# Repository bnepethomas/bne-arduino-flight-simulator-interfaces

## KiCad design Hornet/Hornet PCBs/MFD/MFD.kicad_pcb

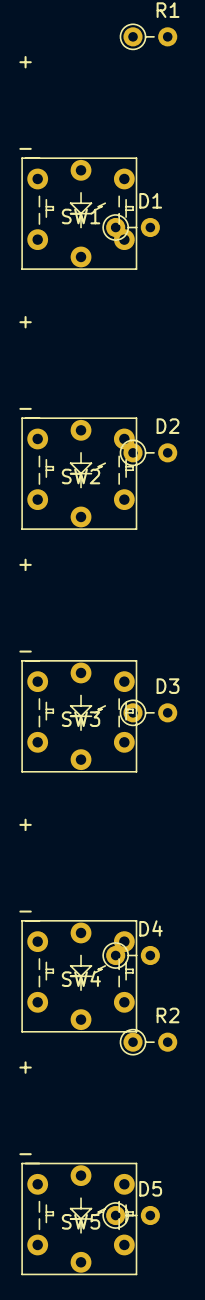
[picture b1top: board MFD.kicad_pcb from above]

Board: 2 copper layers, 12 parts (0 on the bottom side), 13 nets, no tracks yet.

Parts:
D1, D2, D3, D4, D5: D; PT_R_Axial_DIN0204_L3.6mm_D1.6mm_P2.54mm_Vertical
R1, R2: R; PT_R_Axial_DIN0204_L3.6mm_D1.6mm_P2.54mm_Vertical
SW1, SW2, SW3, SW4, SW5: PT_Tactile_Switch_Led; PT_Small_Tactile_Switch_With_LED

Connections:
+12V: R1.2, R2.2
GND: SW3.6, SW5.6
unnamed: D1.1, SW1.1, SW1.2
unnamed: D1.2, D2.2, D3.2, D4.2, D5.2
unnamed: D2.1, SW2.1, SW2.2
unnamed: D3.1, SW3.1, SW3.2
unnamed: D4.1, SW4.1, SW4.2
unnamed: D5.1, SW5.1, SW5.2
unnamed: R1.1, SW1.5
unnamed: R2.1, SW4.5
unnamed: SW1.6, SW2.5
unnamed: SW2.6, SW3.5
unnamed: SW4.6, SW5.5

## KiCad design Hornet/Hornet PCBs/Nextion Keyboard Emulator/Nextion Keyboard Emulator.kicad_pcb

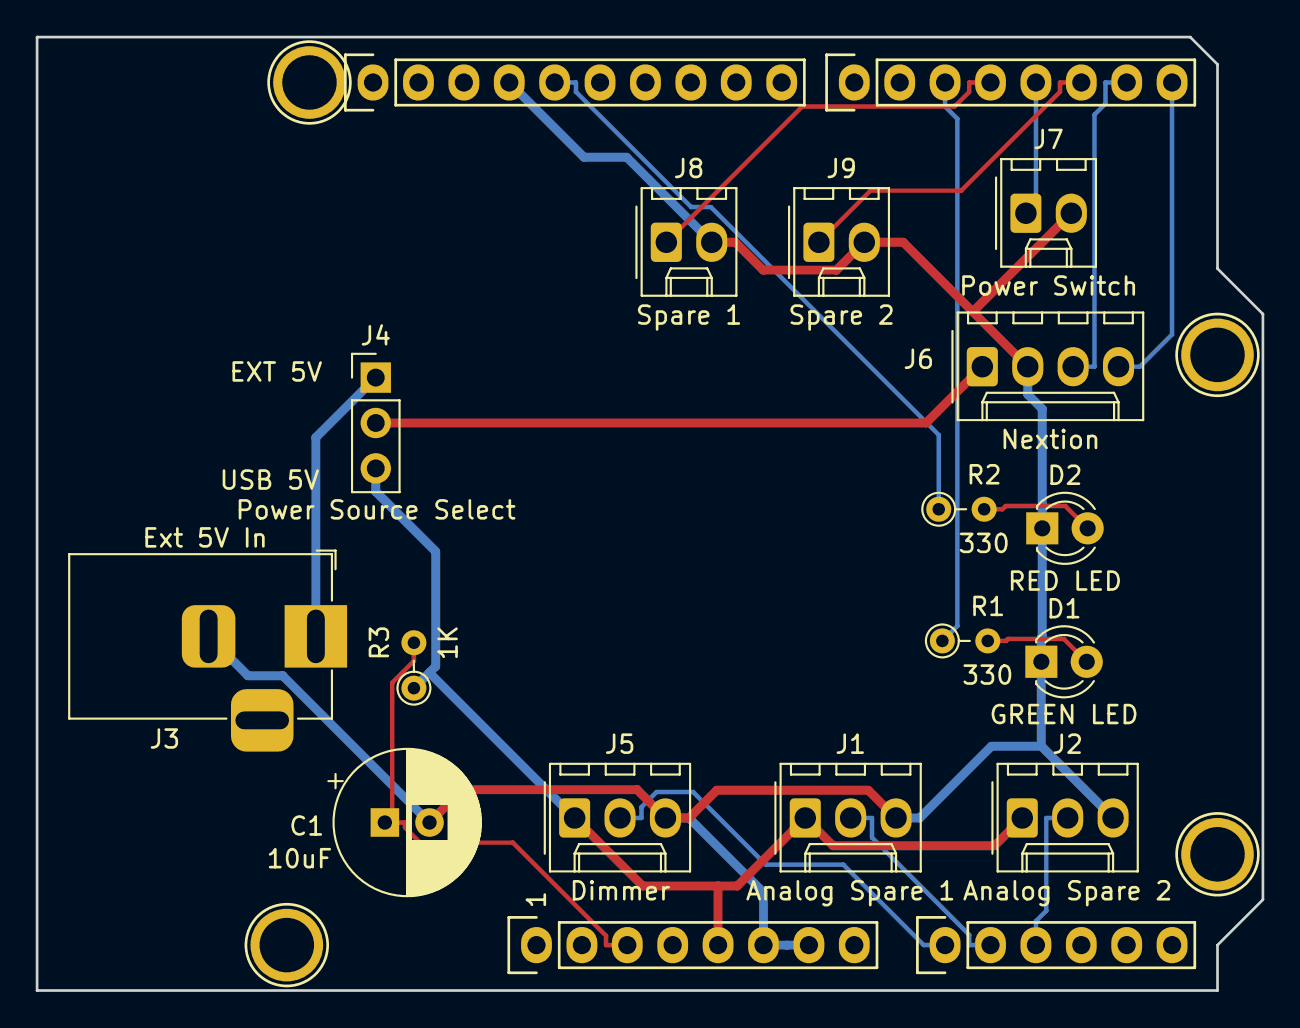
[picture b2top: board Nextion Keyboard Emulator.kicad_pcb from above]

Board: 2 copper layers, 68.6 x 53.3 mm, 23 parts (0 on the bottom side), 17 nets.

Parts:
C1: 10uF; PT_CP_Radial_D8.0mm_P2.50mm
D1: GREEN LED; LED_D3.0mm
D2: RED LED; LED_D3.0mm
J1: Analog Spare 1; Molex_1x03_P2.54mm_Vertical
J2: Analog Spare 2; Molex_1x03_P2.54mm_Vertical
J3: Ext 5V In; BarrelJack_Horizontal
J4: Power Source Select; PinHeader_1x03_P2.54mm_Vertical
J5: Dimmer; Molex_1x03_P2.54mm_Vertical
J6: Nextion; Molex_1x04_P2.54mm_Vertical
J7: Power Switch; Molex_1x02_P2.54mm_Vertical
J8: Spare 1; Molex_1x02_P2.54mm_Vertical
J9: Spare 2; Molex_1x02_P2.54mm_Vertical
P1: Power; Socket_Strip_Arduino_1x08
P2: Analog; Socket_Strip_Arduino_1x06
P3: Digital; Socket_Strip_Arduino_1x10
P4: Digital; Socket_Strip_Arduino_1x08
P5, P6, P7, P8: CONN_01X01; Arduino_1pin
R1, R2: 330; PT_R_Axial_DIN0204_L3.6mm_D1.6mm_P2.54mm_Vertical
R3: 1K; PT_R_Axial_DIN0204_L3.6mm_D1.6mm_P2.54mm_Vertical

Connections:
+5V: J1.1, J2.1, J4.3, J5.1, P1.5, R3.1
+5VD: J4.2, J6.1
/0(Rx): J6.4, P4.8
/1(Tx): J6.3, P4.7
/2: J9.1, P4.6
/3(**): J7.1, P4.5
/4: J8.1, P4.4
/5(**): P4.3, R1.1
/13(SCK): P3.5, R2.1
/A0: J5.2, P2.1
/A1: J1.2, P2.2
/A2: J2.2, P2.3
/EXT5VIN: J3.1, J4.1
/Reset: C1.1, P1.3, R3.2
GND: C1.2, D1.1, D2.1, J1.3, J2.3, J3.2, J5.3, J6.2, J7.2, J8.2, J9.2, P1.6, P1.7, P3.4
unnamed: D1.2, R1.2
unnamed: D2.2, R2.2

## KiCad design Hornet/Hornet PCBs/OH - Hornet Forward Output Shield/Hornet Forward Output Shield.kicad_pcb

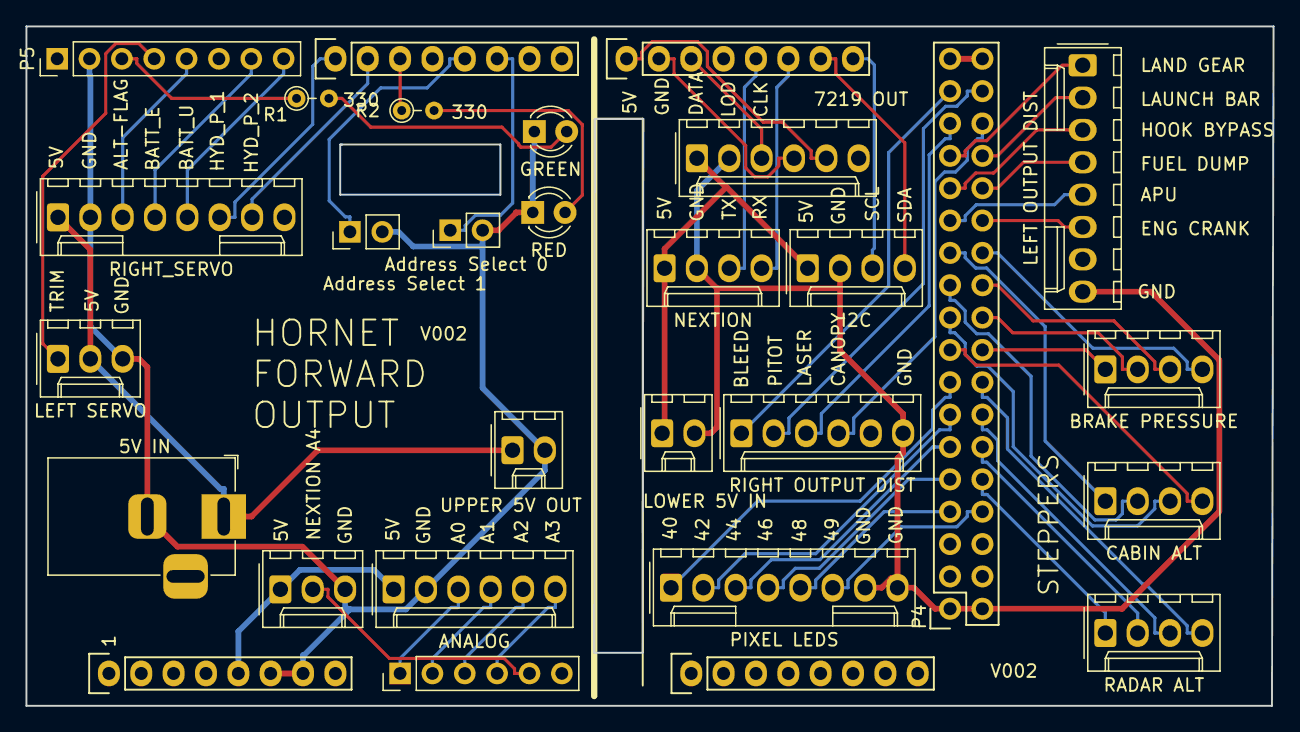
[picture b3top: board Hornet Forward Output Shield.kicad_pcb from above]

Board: 2 copper layers, 97.9 x 53.3 mm, 29 parts (0 on the bottom side), 58 nets.

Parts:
D1: GREEN; LED_D3.0mm
D2: RED; LED_D3.0mm
J1: LEFT OUTPUT DIST; Molex_1x08_P2.54mm_Vertical
J2: RIGHT OUTPUT DIST; Molex_1x06_P2.54mm_Vertical
J3: LEFT SERVO; Molex_1x03_P2.54mm_Vertical
J4: RIGHT_SERVO; Molex_1x08_P2.54mm_Vertical
J5: LOWER 5V IN; Molex_1x02_P2.54mm_Vertical
J6: UPPER 5V OUT; Molex_1x02_P2.54mm_Vertical
J7: NEXTION; Molex_1x04_P2.54mm_Vertical
J8: 7219 OUT; Molex_1x06_P2.54mm_Vertical
J9: PIXEL LEDS; Molex_1x08_P2.54mm_Vertical
J10: I2C; Molex_1x04_P2.54mm_Vertical
J11: 5V IN; BarrelJack_Horizontal
J12: CABIN ALT; Molex_1x04_P2.54mm_Vertical
J13: BRAKE PRESSURE; Molex_1x04_P2.54mm_Vertical
J14: RADAR ALT; Molex_1x04_P2.54mm_Vertical
J15: ANALOG; Molex_1x06_P2.54mm_Vertical
J16: Address Select 0; PinHeader_1x02_P2.54mm_Vertical
J17: Address Select 1; PinHeader_1x02_P2.54mm_Vertical
J18: NEXTION ANA; Molex_1x03_P2.54mm_Vertical
P1: Power; Socket_Strip_Arduino_1x08
P2: Analog; PinHeader_1x06_P2.54mm_Vertical
P3: Analog; Socket_Strip_Arduino_1x08
P4: Digital; Socket_Strip_Arduino_2x18
P5: PWM; PinHeader_1x08_P2.54mm_Vertical
P6: PWM; Socket_Strip_Arduino_1x08
P7: Communication; Socket_Strip_Arduino_1x08
R1, R2: 330; PT_R_Axial_DIN0204_L3.6mm_D1.6mm_P2.54mm_Vertical

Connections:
+5V: P4.35, P4.36
+5VL: J15.1, J18.1, P1.5
/14(Tx3): J8.5, P7.1
/15(Rx3): J8.4, P7.2
/16(Tx2): J8.3, P7.3
/18(Tx1): J7.3, P7.5
/19(Rx1): J7.4, P7.6
/20(SDA): J10.4, P7.7
/21(SCL): J10.3, P7.8
/22: J2.1, P4.33
/23: J2.2, P4.34
/24: J2.3, P4.31
/25: J2.4, P4.32
/26: J1.1, P4.29
/27: J1.2, P4.30
/28: J1.3, P4.27
/29: J1.4, P4.28
/30: J1.5, P4.25
/31: J1.6, P4.26
/32: J12.1, P4.23
/33: J13.4, P4.24
/34: J12.2, P4.21
/35: J13.3, P4.22
/36: J12.3, P4.19
/37: J13.2, P4.20
/38: J12.4, P4.17
/39: J13.1, P4.18
/40: J9.1, P4.15
/41: J14.4, P4.16
/42: J9.2, P4.13
/43: J14.3, P4.14
/44: J9.3, P4.11
/45: J14.2, P4.12
/46: J9.4, P4.9
/47: J14.1, P4.10
/48: J9.5, P4.7
/49: J9.6, P4.8
/A0: J15.3, P2.1
/A1: J15.4, P2.2
/A2: J15.5, P2.3
/A3: J15.6, P2.4
/A4: J18.2, P2.5
/ADDRESS_SELECT_0: J16.1, P6.6
/ADDRESS_SELECT_1: J17.1, P6.5
/D5: P6.3, R2.1
/D6: J4.7, P6.2
/D7: J4.6, P6.1
/D8: J4.5, P5.8
/D9: J4.4, P5.7
/D11: J4.3, P5.5
/D12: J3.1, P5.4
/D13: P5.3, R1.1
/LOWER_OUTPUT_5V: J5.1, J7.1, J8.1, J10.1
/UPPER_OUTPUT_5V: J3.2, J4.1, J6.1, J11.1
GND: J1.8, J2.6, J5.2, J7.2, J8.2, J9.7, J9.8, J10.2, P4.1, P4.2
GNDD: D1.1, D2.1, J3.3, J4.2, J6.2, J11.2, J15.2, J16.2, J17.2, J18.3, P1.6, P1.7, P5.2
unnamed: D1.2, R1.2
unnamed: D2.2, R2.2

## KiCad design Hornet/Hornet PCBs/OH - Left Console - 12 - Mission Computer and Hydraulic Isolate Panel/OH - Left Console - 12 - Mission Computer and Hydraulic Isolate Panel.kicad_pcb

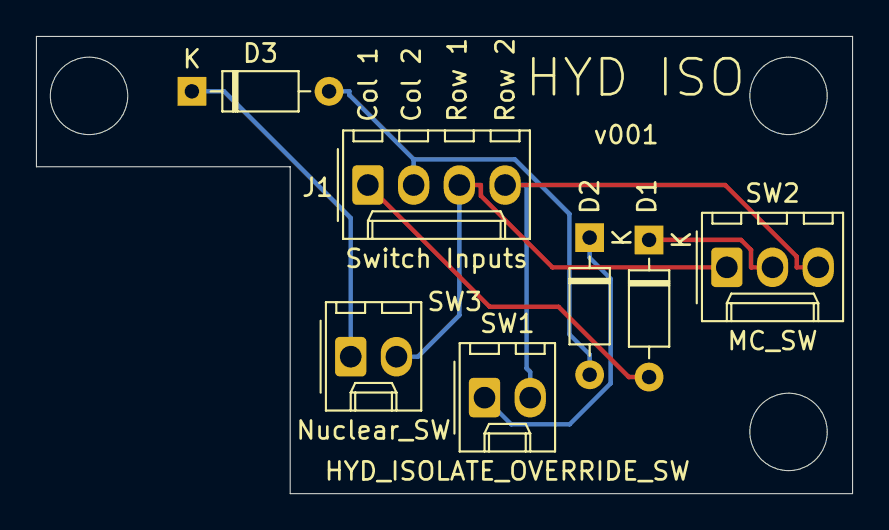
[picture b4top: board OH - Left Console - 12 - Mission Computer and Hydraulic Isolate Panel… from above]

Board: 2 copper layers, 45.3 x 25.4 mm, 10 parts (0 on the bottom side), 7 nets.

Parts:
D1, D2, D3: D; D_Signal_P7.62mm_Horizontal
H1, H2, H3: MountingHole; MountingHole_4.3mm_M4
J1: Switch Inputs; Molex_1x04_P2.54mm_Vertical
SW1: HYD_ISOLATE_OVERRIDE_SW; Molex_1x02_P2.54mm_Vertical
SW2: MC_SW; Molex_1x03_P2.54mm_Vertical
SW3: Nuclear_SW; Molex_1x02_P2.54mm_Vertical

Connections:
/Col1: D1.2, J1.1
/Col2: D2.2, D3.2, J1.2
/Row1: J1.3, SW2.1, SW3.2
/Row2: J1.4, SW1.2, SW2.3
unnamed: D1.1, SW2.2
unnamed: D2.1, SW1.1
unnamed: D3.1, SW3.1

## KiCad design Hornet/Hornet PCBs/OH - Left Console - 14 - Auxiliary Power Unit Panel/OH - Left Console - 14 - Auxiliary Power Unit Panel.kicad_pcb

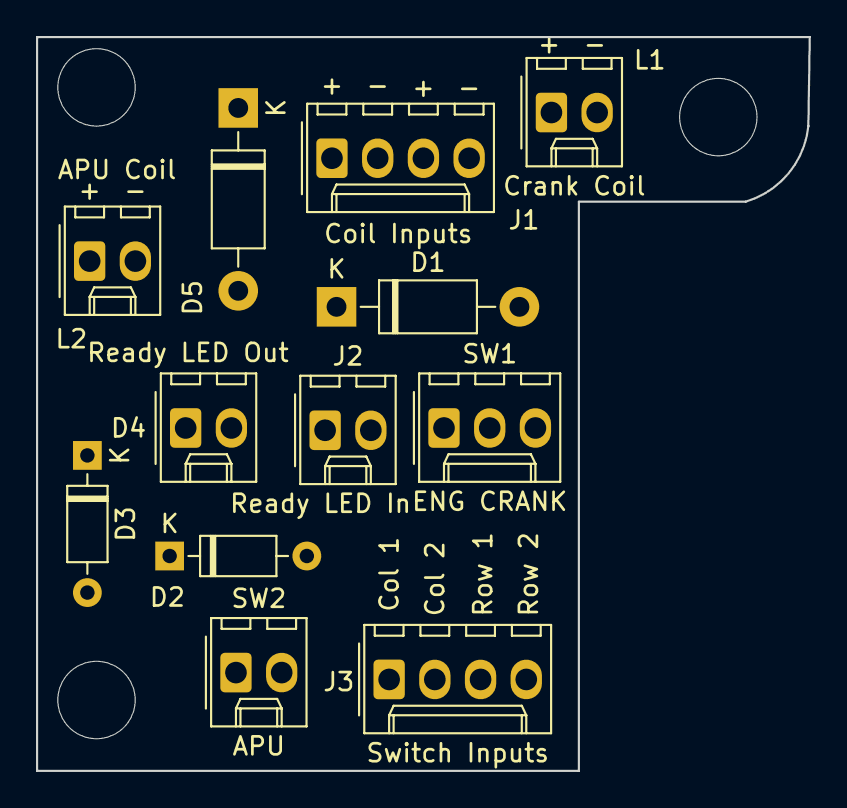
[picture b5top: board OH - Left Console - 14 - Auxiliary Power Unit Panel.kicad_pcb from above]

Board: 2 copper layers, 42.9 x 40.8 mm, 15 parts (0 on the bottom side), 12 nets, no tracks yet.

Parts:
D1, D5: D; D_DO-41_SOD81_P10.16mm_Horizontal
D2, D3: D; D_Signal_P7.62mm_Horizontal
D4: Ready LED Out; Molex_1x02_P2.54mm_Vertical
H1, H2, H3: MountingHole; MountingHole_4.3mm_M4
J1: Coil Inputs; Molex_1x04_P2.54mm_Vertical
J2: Ready LED In; Molex_1x02_P2.54mm_Vertical
J3: Switch Inputs; Molex_1x04_P2.54mm_Vertical
L1: Crank Coil; Molex_1x02_P2.54mm_Vertical
L2: APU Coil; Molex_1x02_P2.54mm_Vertical
SW1: ENG CRANK; Molex_1x03_P2.54mm_Vertical
SW2: APU; Molex_1x02_P2.54mm_Vertical

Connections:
/Col1: D2.2, J3.1
/Col2: D3.2, J3.2
/Row1: J3.3, SW1.1, SW2.2
/Row2: J3.4, SW1.3
unnamed: D1.1, J1.3, L1.1
unnamed: D1.2, J1.4, L1.2
unnamed: D2.1, SW1.2
unnamed: D3.1, SW2.1
unnamed: D4.1, J2.2
unnamed: D4.2, J2.1
unnamed: D5.1, J1.1, L2.1
unnamed: D5.2, J1.2, L2.2

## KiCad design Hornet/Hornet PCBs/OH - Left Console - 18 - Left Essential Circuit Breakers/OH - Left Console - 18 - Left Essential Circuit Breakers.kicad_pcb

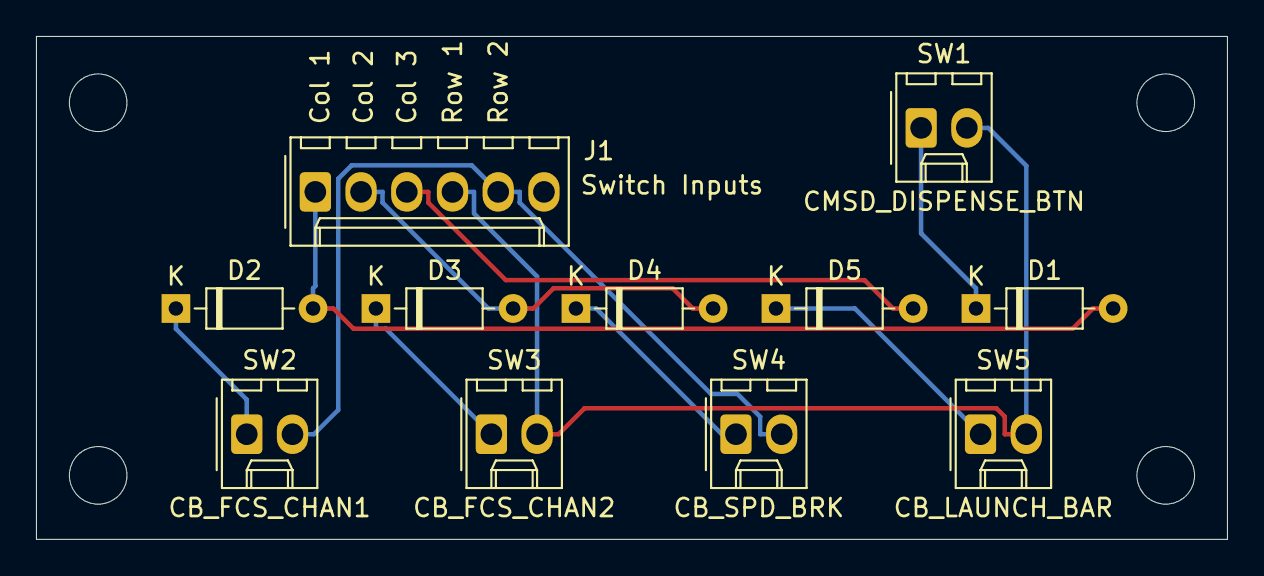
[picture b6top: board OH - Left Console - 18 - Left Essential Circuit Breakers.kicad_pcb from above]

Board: 2 copper layers, 66.2 x 27.9 mm, 15 parts (0 on the bottom side), 10 nets.

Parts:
D1, D2, D3, D4, D5: D; D_Signal_P7.62mm_Horizontal
H1, H2, H3, H4: MountingHole; MountingHole_3.2mm_M3
J1: Switch Inputs; Molex_1x06_P2.54mm_Vertical
SW1: CMSD_DISPENSE_BTN; Molex_1x02_P2.54mm_Vertical
SW2: CB_FCS_CHAN1; Molex_1x02_P2.54mm_Vertical
SW3: CB_FCS_CHAN2; Molex_1x02_P2.54mm_Vertical
SW4: CB_SPD_BRK; Molex_1x02_P2.54mm_Vertical
SW5: CB_LAUNCH_BAR; Molex_1x02_P2.54mm_Vertical

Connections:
/Col1: D1.2, D2.2, J1.1
/Col2: D3.2, D4.2, J1.2
/Col3: D5.2, J1.3
/Row1: J1.4, SW1.2, SW3.2, SW5.2
/Row2: J1.5, SW2.2, SW4.2
unnamed: D1.1, SW1.1
unnamed: D2.1, SW2.1
unnamed: D3.1, SW3.1
unnamed: D4.1, SW4.1
unnamed: D5.1, SW5.1

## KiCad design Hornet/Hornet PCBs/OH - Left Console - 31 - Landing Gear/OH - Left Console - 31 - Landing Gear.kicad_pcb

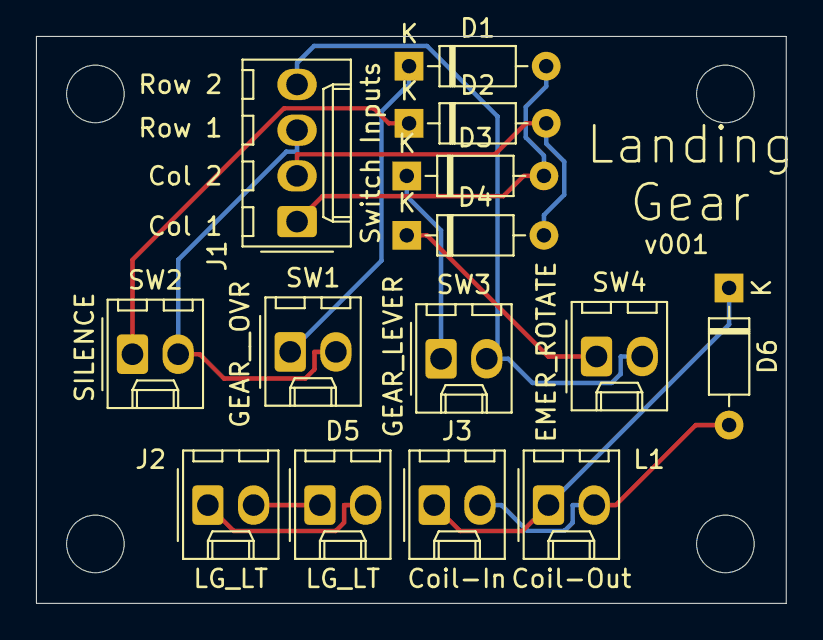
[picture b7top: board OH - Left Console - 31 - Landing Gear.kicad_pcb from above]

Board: 2 copper layers, 41.7 x 31.5 mm, 18 parts (0 on the bottom side), 12 nets.

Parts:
D1, D2, D3, D4, D6: D; D_Signal_P7.62mm_Horizontal
D5: LG_LT; Molex_1x02_P2.54mm_Vertical
H1, H2, H3, H4: MountingHole; MountingHole_3.2mm_M3
J1: Switch Inputs; Molex_1x04_P2.54mm_Vertical
J2: LG_LT; Molex_1x02_P2.54mm_Vertical
J3: Coil-In; Molex_1x02_P2.54mm_Vertical
L1: Coil-Out; Molex_1x02_P2.54mm_Vertical
SW1: GEAR__OVR; Molex_1x02_P2.54mm_Vertical
SW2: SILENCE; Molex_1x02_P2.54mm_Vertical
SW3: GEAR_LEVER; Molex_1x02_P2.54mm_Vertical
SW4: EMER_ROTATE; Molex_1x02_P2.54mm_Vertical

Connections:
/Col1: D1.2, D3.2, J1.1
/Col2: D2.2, D4.2, J1.2
/Row1: J1.3, SW1.2, SW2.2
/Row2: J1.4, SW3.2, SW4.2
unnamed: D1.1, SW1.1
unnamed: D2.1, SW2.1
unnamed: D3.1, SW3.1
unnamed: D4.1, SW4.1
unnamed: D5.1, J2.2
unnamed: D5.2, J2.1
unnamed: D6.1, J3.1, L1.1
unnamed: D6.2, J3.2, L1.2

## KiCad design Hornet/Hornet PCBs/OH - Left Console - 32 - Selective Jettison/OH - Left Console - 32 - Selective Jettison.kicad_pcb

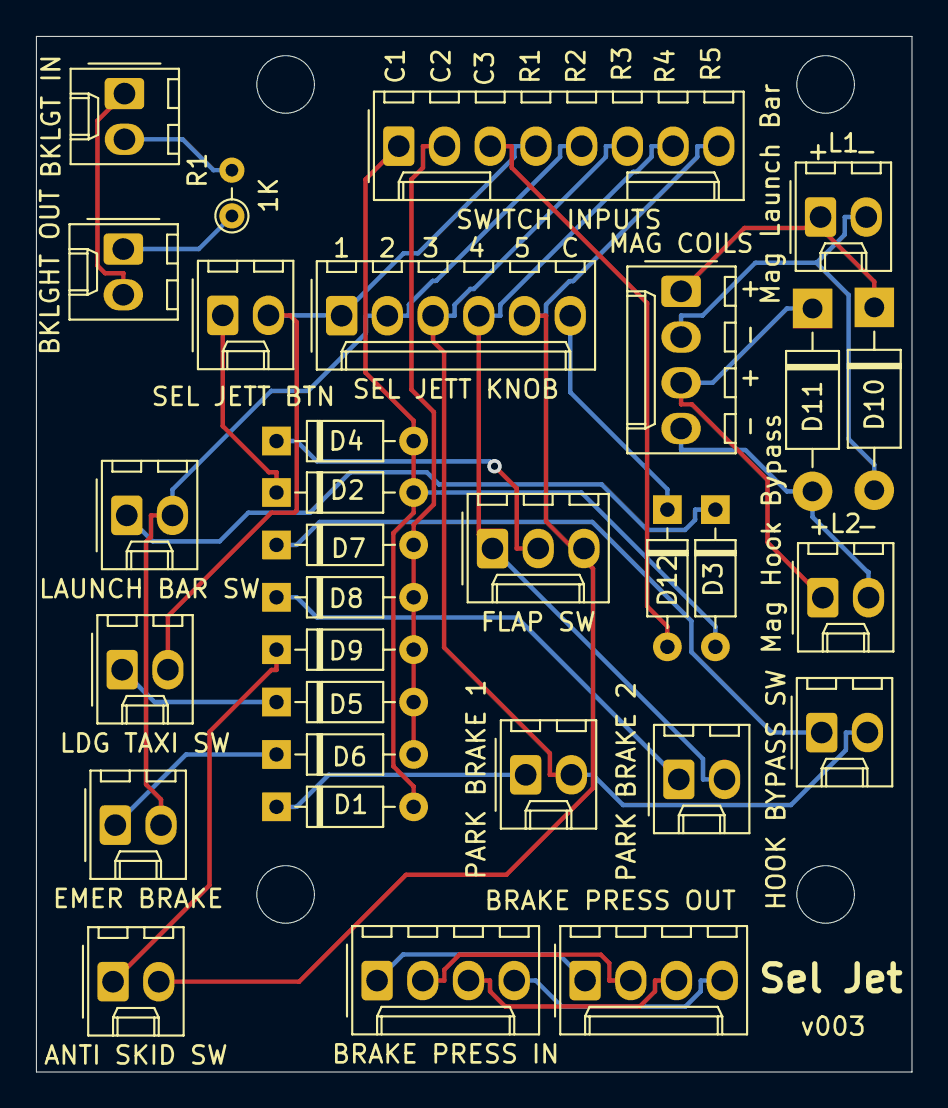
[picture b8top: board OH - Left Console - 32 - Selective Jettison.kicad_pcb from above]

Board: 2 copper layers, 48.6 x 57.5 mm, 35 parts (0 on the bottom side), 29 nets.

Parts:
D1, D2, D3, D4, D5, D6, D7, D8, D9, D12: D; D_Signal_P7.62mm_Horizontal
D10, D11: D; D_DO-41_SOD81_P10.16mm_Horizontal
H1, H2, H3, H4: MountingHole; MountingHole_3.2mm_M3
J1: BRAKE PRESS OUT; Molex_1x04_P2.54mm_Vertical
J2: BRAKE PRESS IN; Molex_1x04_P2.54mm_Vertical
J3: MAG COILS; Molex_1x04_P2.54mm_Vertical
J4: SWITCH INPUTS; Molex_1x08_P2.54mm_Vertical
J5: BKLGT IN; Molex_1x02_P2.54mm_Vertical
J6: BKLGHT OUT; Molex_1x02_P2.54mm_Vertical
L1: Mag Launch Bar; Molex_1x02_P2.54mm_Vertical
L2: Mag Hook Bypass; Molex_1x02_P2.54mm_Vertical
R1: 1K; PT_R_Axial_DIN0204_L3.6mm_D1.6mm_P2.54mm_Vertical
SW1: SEL JETT BTN; Molex_1x02_P2.54mm_Vertical
SW2: LAUNCH BAR SW; Molex_1x02_P2.54mm_Vertical
SW3: PARK BRAKE 1; Molex_1x02_P2.54mm_Vertical
SW4: FLAP SW; Molex_1x03_P2.54mm_Vertical
SW5: HOOK BYPASS SW; Molex_1x02_P2.54mm_Vertical
SW6: PARK BRAKE 2; Molex_1x02_P2.54mm_Vertical
SW7: ANTI SKID SW; Molex_1x02_P2.54mm_Vertical
SW8: LDG TAXI SW; Molex_1x02_P2.54mm_Vertical
SW9: EMER BRAKE; Molex_1x02_P2.54mm_Vertical
SW10: SEL JETT KNOB; Molex_1x06_P2.54mm_Vertical

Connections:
/COL1: D1.2, D2.2, D3.2, D4.2, J4.1
/COL2: D5.2, D6.2, D7.2, D8.2, D9.2, J4.2
/COL3: D12.2, J4.3
/MAG_1_+: D10.1, J3.1, L1.1
/MAG_1_-: D10.2, J3.2, L1.2
/MAG_2_+: D11.1, J3.3, L2.1
/MAG_2_-: D11.2, J3.4, L2.2
/ROW1: J4.4, SW1.2, SW8.2, SW10.1
/ROW2: J4.5, SW2.2, SW9.2, SW10.2
/ROW3: J4.6, SW3.2, SW5.2, SW10.3
/ROW4: J4.7, SW4.1, SW6.2, SW10.4
/ROW5: J4.8, SW4.3, SW7.2, SW10.5
unnamed: D1.1, SW3.1
unnamed: D2.1, SW1.1
unnamed: D3.1, SW2.1
unnamed: D4.1, SW4.2
unnamed: D5.1, SW8.1
unnamed: D6.1, SW9.1
unnamed: D7.1, SW5.1
unnamed: D8.1, SW6.1
unnamed: D9.1, SW7.1
unnamed: D12.1, SW10.6
unnamed: J1.1, J2.1
unnamed: J1.2, J2.2
unnamed: J1.3, J2.3
unnamed: J1.4, J2.4
unnamed: J5.1, J6.2
unnamed: J5.2, R1.2
unnamed: J6.1, R1.1
